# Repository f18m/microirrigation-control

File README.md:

# Micro-irrigation Control #

This project contains source code for:
 - a Linux embedded system (in my case Olimex Lime2 A20 single board computer)
 - digital radio transceivers (in my case a couple of Texas Instruments CC1110 boards)

The aim of the system is to provide via a web interface the possibility to open or close remote relays,
which in my casea are attached to electrovalves that open or close some water flows (in my case to provide
irrigation in my garden).
However the target of the system is much more generic and you can attach to the "remote" node pretty much
anything you like.

## Prerequisites ##

This project assumes that you have:
1. an embedded Linux system, in particular Olimex Lime2 is assumed here.
   Moreover I tested this project only with a recent Debian-variant "armbian" installed, using DeviceTree overlays for
   accessing the SPI bus of the embedded system. See https://docs.armbian.com/User-Guide_Allwinner_overlays/.
   The DeviceTree config file used in my case is [available here](software-lime2/lime2_device_tree/armbianEnv.txt).
2. two digital radios, based on Texas Instruments CC1110, operating in the 433 or 868/915 Mhz ISM bands.
   See e.g., http://www.ti.com/tool/CC1110EMK868-915 for the commercial boards used in this project.
   This choice is motivated by the fact that these frequencies provide high wall penetration and low battery 
   consumption compared to other radio technologies like the well-known Wi-Fi.

## Architecture ##

This picture gives an overview of the whole system:

## Hardware Design ##

The hardware design for the remote node is available as Cadsoft Eagle schematics (see https://www.autodesk.com/products/eagle/overview)
in the hardware-remote folder. The design is based on 3 major parts:
1) the CC1110 evaluation module which provides the antenna, the CC1110 radio+micro and its programming interface. 
   See http://www.ti.com/tool/CC1110EMK868-915 ; this can be connected via SPI bus to an embedded SoC Linux system
   like a Raspberry Pi or similar boards. I used the Olimex Lime2. I documented the [wiring between the CC1110 board and the Lime2](docs/wiring-cc1110-lime2.md).
2) one or more commercial relay boards. These are usually unbranded chinese boards which you can find by googling 
   for e.g. "DC 12V 2CH isolated high low level trigger relay module". Here's a picture of the one I used:
   
   The important aspect to keep in mind is that in my hardware design the CC1110 will drive the inputs of these
   relay modules directly (thus applying 3.3V as logic high signal) so that they must be both opto-isolated and
   sensitive enough (most modules out there expect 5V as logic high signal).
3) a custom "glue" board to provide right power and cabling between the other 2 parts. 
   I built this on a simple stripboard (https://en.wikipedia.org/wiki/Stripboard).
   This board connects the battery source (a 12V lead-acid battery in my case) to the radio module and relay module.

This is the overview of the custom glue board (extremely simple):

Finally a small caveat: typical electrovalves will require a positive pulse to move the internal valve to the OPEN
position and a negative pulse to go in the CLOSE position. This requires the driving hardware to be able to 
invert the output polarity. This can be achieved using 2 channels of a relay module and wiring the electrovalve
as shown in this picture:

Note that the normally-open (NO) contacts are attached to the 12V battery while the normally-closed (NC) contacts
are attached to the ground. When no signal is applied to the relay module, the electrovalve has both its wires
connected to the 12V and thus no current circulates. When one of the relay modules is triggered then the electrovalve
will receive +12V or -12V. Thus the polarity applied to the electrovalve can be controlled by triggering just one 
of the 2 relay channels.

## Battery Duration ##

The current consumption budget of the remote node when the firmware puts the radio in sleep mode is:
 - 100 uA for the 12V to 3V current regulator (in the hardware schematic shown above an ADP3333 low dropout 300mA-max regulator was chosen)
 - 130 uA for the static resistor divider used for battery voltage probing
 - 0.5 uA for the CC1110 (considering the power mode 2 used by the firmware of this project)

For a total consumption of about 240uA.
The current consumption budget of the remote node when the firmware puts the radio in RX mode is dominated by the CC1110 
and will be around 22mA. With current firmware settings the RX window lasts for about 3sec.
Of course the "remote" node also needs to transmit an acknowledge to the "lime2" node (when a command is received in that RX window)
raising current consumption up to 36mA but the TX time is so short that can be neglected in computations.

Assuming that a 7Ah lead-acid battery is used for powering the system, and that the sensor will wake up once every 6 seconds to check for
commands over the radio channel, the battery life can be easily computed using e.g. https://oregonembedded.com/batterycalc.htm.

Data entered on that page is thus (considering current firmware version in this Github project):
 - 7000mAh capacity rating
 - 100uA + 130uA + 0.5uA  ~0.240mA current consumption of device during sleep
 - ~22mA current consumption of device during wake (radio in RX mode)
 - 3600sec / (6sec + 3sec) = 400 number of wakeups per hour
 - 3000 ms duration of wake time
 
The result is a battery duration of **~33 days**.

The computations above do not include of course the current consumed to actually activate the relays and to move the
electrovalve from the OPEN to the CLOSE position or viceversa. However such event is typically very rare (let's say once per day)
and thus can be ignored to simplify computation.

Of course it's clear that the more the remote node remains in sleep mode the longer the battery will last. This resolves to a basic
tradeoff in the design criteria: by increasing the sleep time the battery life is increased but the latency for delivering commands
from the lime2 node to the remote node increases as well.

## Firmware and Software Design ##

Both the remote node and the lime2 nodes have custom firmware written in C and based upon Texas Instruments BSP and MRFI packages for CC1110
(its datasheet is available on Texas Instruments website at http://www.ti.com/lit/ds/symlink/cc1110-cc1111.pdf)
The directory with the source code is "firmware-cc1110-lime2-remote"; it contains a project for the [IAR Embedded Workbench for 8051](https://www.iar.com/iar-embedded-workbench/) IDE. Unfortunately if you need to change it (you will probably need unless you use exactly
the same evaluation module from TI with the same pinout), you have to either buy the IAR software or use the 30days evaluation trial;
indeed the 4-kb limited edition is not suitable for any project employing CC1110 radio.

The firmware can be built in 2 modes: REMOTE and LIME2 to produce the firmware for the 2 peers of this project.
[SPI protocol](docs/spi-protocol-cc1110-lime2.md) documentation is available and provides an overview of supported SPI commands.
[Radio protocol](docs/radio-protocol.md) documentation is available as well.

The firmware logic of the LIME2 node can be summarized as follows:
 - poll the SPI RX buffer looking for commands
 - whenever an SPI TURNON/TURNOFF command is received from the Lime2 Linux system, then a radio packet is filled with that command 
   and sent (there is no real addressing logic: we assume only 1 receiver will be present); 
   for each transmitted command, the system waits for an over-radio acknowledge and, if that arrives, the data contained in the
   acknowledge packet is saved; if it does not arrive, the command is retransmitted until the acknowledge arrives;
 - whenever an SPI STATUS command is received from the Lime2 Linux, then the data contained from the most recent acknowledge packet
   is provided to the Lime2 Linux.
   
In practice the LIME2 node acts as an SPI-to-radio bridge.
The presence of the "transaction ID" in both command packets and acknowledge packets allows all parts of the system to discard duplicates
(e.g. the remote node can discard multiple commands having the same transaction IDs, which may be transmitted by the lime2 node when 
the acknowledge packet gets lost) and the Lime2 Linux system to understand if a command has been successfully received by the remote node.

The firmware logic of the REMOTE node can be summarized as follows:
 - sleep for a certain amount of time, using a low-power timer to wake up the MCU;
 - when the MCU wakes up, the radio is turned on in RX mode and the remote node waits for a certain time window for incoming commands;
 - whenever a radio TURNON/TURNOFF command is received from the Lime2 node, then the command data is saved and an acknowledge
   radio packet is generated and transmitted; the system then waits some time to allow the Lime2 node to receive the acknowledge and
   stop repeating the command. After such "cool down" time window, the remote node drives its GPIO pins to turn on/off the relay modules
   which in turn will open/close the electrovalves.

The presence of the ADC read of the battery in each acknowledge allows to exploit the uplink channel remote->lime2 node to also 
provide an indication of how much battery power is left.

## Source code ##

Tree of contained source code is:

```
 firmware-cc1110-lime2-remote:  this is the firmware written in C for both the CC1110 "lime2" node and the "remote" node. 
  \-- source
       \-- apps    
            \-- lime2.c: contains the firmware source code for the node attached to the Linux embedded system over SPI
                remote.c: contains the firmware source code for the node attached to the electrovalve
  
 software-lime2: this is the PHP code for the Linux embedded system
  \-- spidev_test:  this is the Linux kernel utility written in C that provide an easy way to communicate with devices over SPI
      web:          this folder contains the PHP code implementing the specific communication protocol over-SPI;
                    this code must be run inside a regular web server (e.g. Apache, lighttpd or nginx) and uses a mix of PHP and
                    Javascript to open WebSockets to get updates about SPI activities.
      bin:          this folder contains PHP code to implement a WebSocket server using Ratchet (http://socketo.me/);  
                    the WebSocket server is used by Javascript code to fetch updates from SPI.
```

Main source files to understand the application:

 - [main.c](firmware-cc1110-lime2-remote/source/apps/main.c)
 - [lime2.c](firmware-cc1110-lime2-remote/source/apps/lime2.c)
 - [remote.c](firmware-cc1110-lime2-remote/source/apps/remote.c)

## Installation ##

TO BE WRITTEN

## Final Result ##

This how my final assembly of the remote node looks like:

These are instead a screenshot of the web interface:

It is very very simple and is currently integrated with my other project: http://github.com/f18m/light-media-center

## Project Status ##

As of Aug 2018 I put "on the field" (literally) my assembly with the software and firmare of this GIT repo.
It works well so far. 
I will develop and maintain this project in my free time, though I don't plan to add any new feature.
Eventually I will improve the look and feel of the web interface but that's pretty much it.

## Similar Projects ##

The most comprehensive project similar to this is MySensors: https://www.mysensors.org

Similar projects designed to drive relay boards that are directly connected to the Linux system (without the radio bridge):

- http://www.logicaprogrammabile.it/come-pilotare-elettrovalvola-bistabile-usando-2-rele/ (in Italian)
- https://github.com/ondrej1024/crelay
- https://github.com/darrylb123/usbrelay

Similar projects designed to drive REMOTE relay boards (not BATTERY powered though):
- https://github.com/shanet/RelayRemote

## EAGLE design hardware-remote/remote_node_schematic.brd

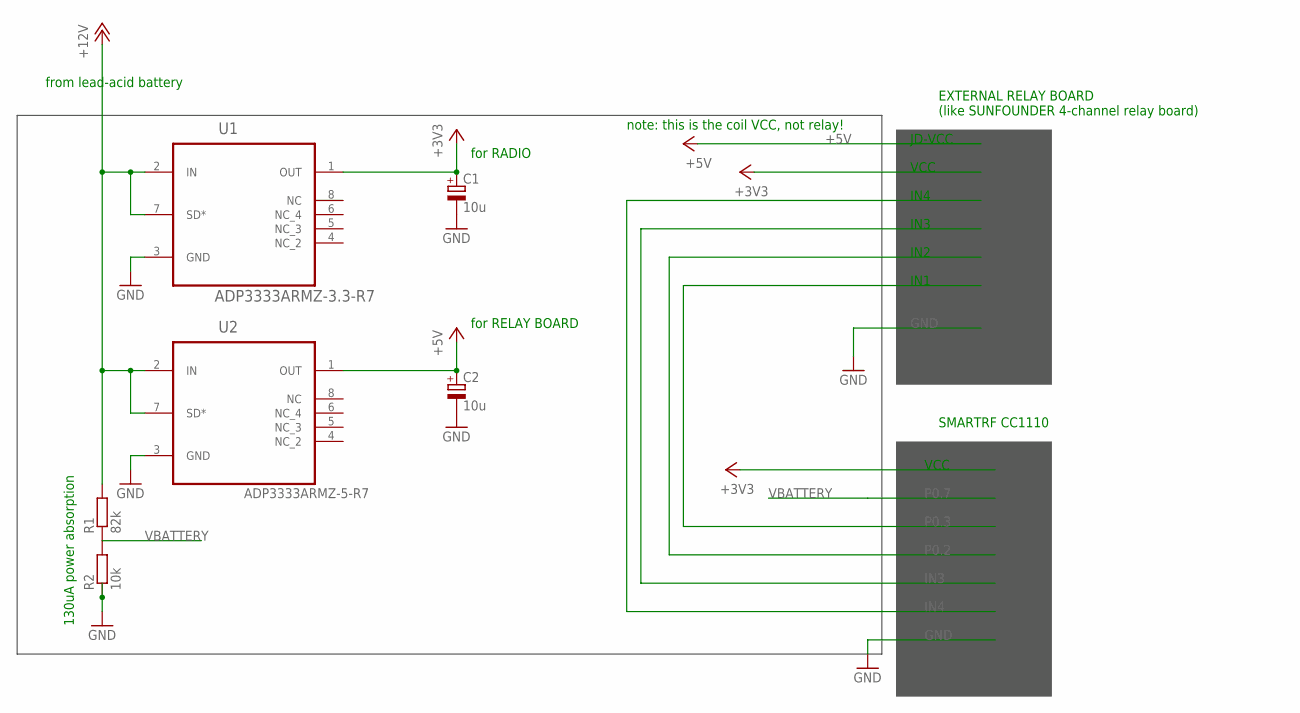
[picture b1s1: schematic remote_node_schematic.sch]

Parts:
C1, C2: 10u; 085CS_1AR
R1: 82k; 0207/10
R2: 10k; 0207/10
U1, U2: ADP3333ARMZ-3.3-R7; SOP65P490X110-8N

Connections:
+3V3: C1.+, U1.1 (OUT)
+9V: C2.+, U2.1 (OUT)
+12V: R1.2, U1.2 (IN), U1.7 (SD*), U2.2 (IN), U2.7 (SD*)
GND: C1.-, C2.-, R2.1, U1.3 (GND), U2.3 (GND)
VBATTERY: R1.1, R2.2

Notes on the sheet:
for RADIO
for RELAY BOARD
EXTERNAL RELAY BOARD (like SUNFOUNDER 4-channel relay board)
JD-VCC
VCC
from lead-acid battery
SMARTRF CC1110
note: this is the coil VCC, not relay!
IN2
IN1
130uA power absorption
IN4
IN3

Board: 2 copper layers, 6 parts (0 on the bottom side), 5 nets, no tracks yet.

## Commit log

2017-09-16 first checkin
2017-09-17 first impl
2017-09-17 support open,close,test modes
2017-10-16 First checkin of firmware
    LIME2 node: the SPI pretty much works
    REMOTE node: the radio system is pretty much working
2017-11-07 Get the project to usable state
    Too many fixes / developments to list
2017-11-07 more desc
2017-11-08 add spidev_test utility
2017-11-08 use spidev_test directly from PHP
2017-11-13 create a PHP lib to handle SPI communication with radio
2017-11-13 Create a better defined structure for the WEB part. Introduce basic WebSocket experimental code
2017-11-18 Fix PHP root permission issue by having the WebSocket server run as root instead of trying to run privileged commands from the webserver
2017-11-18 support also TURNOFF command
2017-11-18 add architecture picture
2017-11-18 fix source tree
2017-11-21 add SystemD init file
2017-11-25 add HW design docs
2017-11-25 try to fix arch png
2018-04-28 add battery measurements
2018-04-28 add some docs
2018-04-28 fix formatting
2018-05-12 add ignore
2018-05-12 more ignore
2018-05-12 improve REMOTE firmware
2018-05-14 provide much more output in the CLI test utility
2018-05-14 give battery read also from CLI utility
2018-08-17 more details on the packet format
2018-08-17 fix link
2018-08-17 support command parameter for TURNON and TURNOFF
2018-08-17 add support to drive 2 relay channels independently
2018-08-18 more hw docs
2018-08-18 Use JSON from JavaScript to the PHP server; make CLI backend more flexible by integrating better commandline parsing and error checks; add auto-off feature after X minutes.
2018-08-18 add loglevels; hide DEBUG logs
2018-08-18 more docs
2018-08-18 add screenshot of web interface
2018-08-19 add wiring of SPI bus
2018-11-04 Update firmware with new NOOP command to get battery level
2018-11-04 update battery measurements
2018-11-04 add NOOP and GET_BATTERY_LEVEL commands
